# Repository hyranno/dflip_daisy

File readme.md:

WIP keyboard design

## Required Kicad Plugins (Manually via PCM):
* com.github.perigoso.keyswitch-kicad-library
* com.github.gauravmm.hierarchicalpcb
* com.github.yaqwsx.kikit

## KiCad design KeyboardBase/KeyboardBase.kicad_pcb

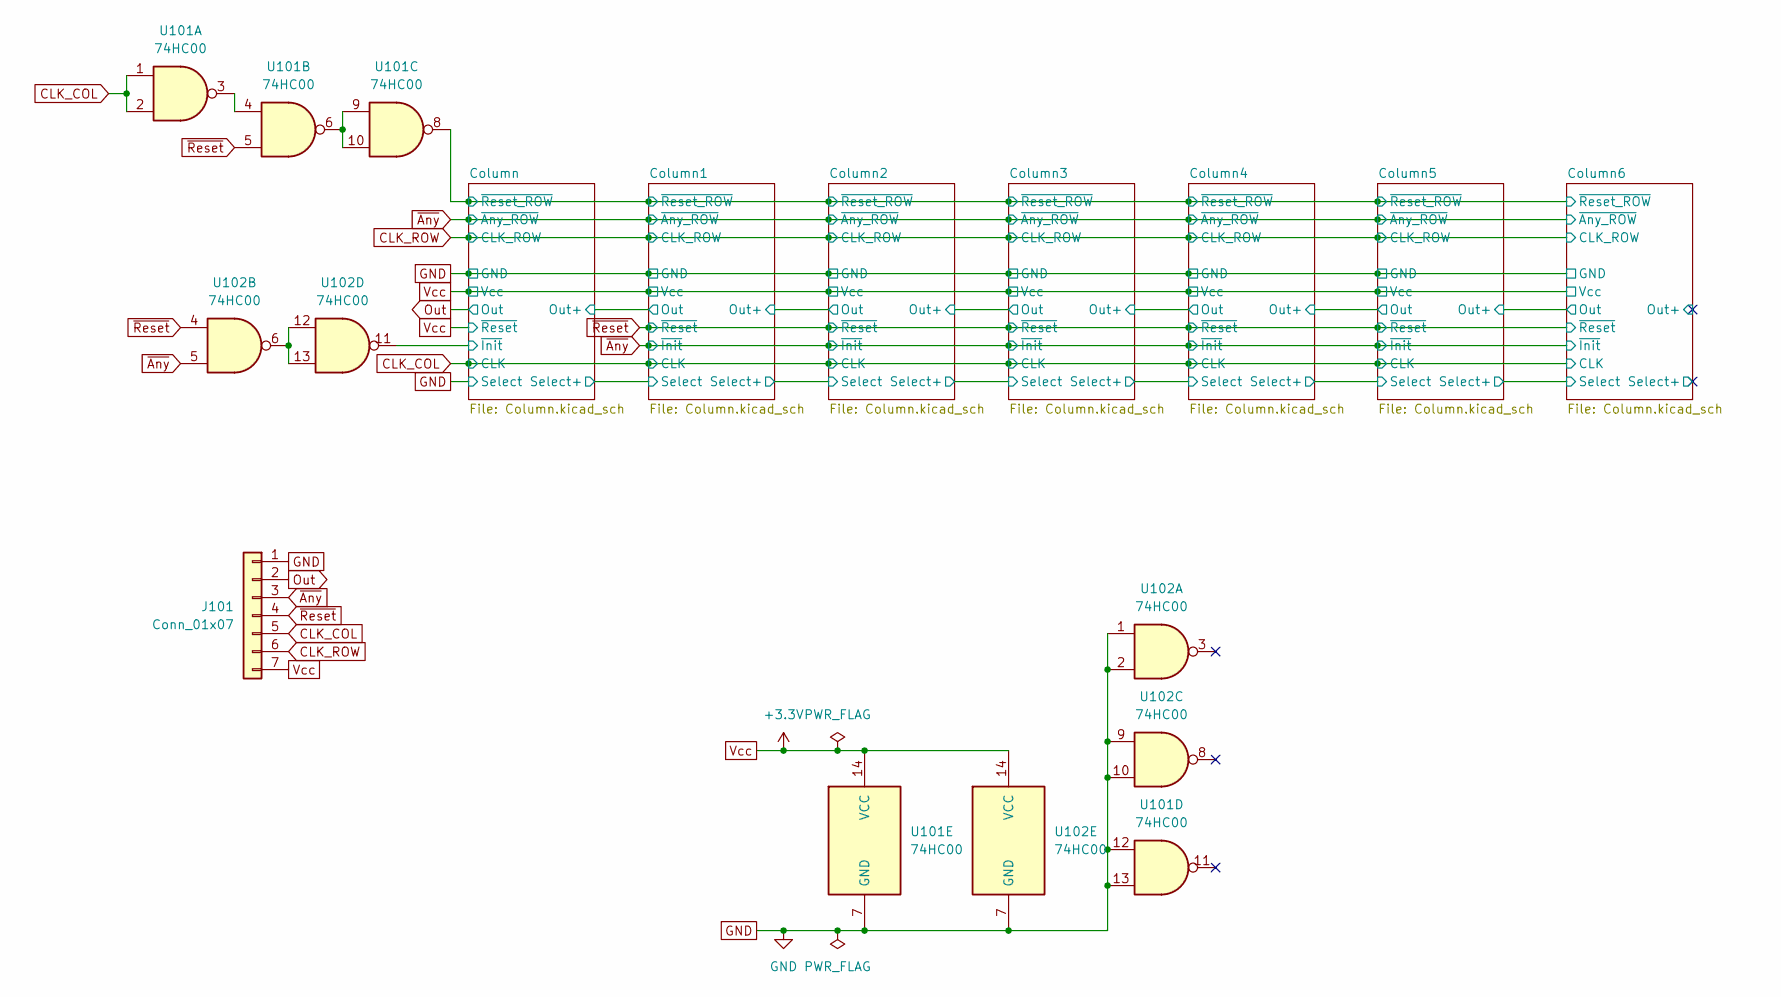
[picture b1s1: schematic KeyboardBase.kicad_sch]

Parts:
J101: Conn_01x07; PinHeader 2.00mm 01x07 SMD
U101, U102: 74HC00; WQFN-14-1EP_2.5x2.5mm_P0.5mm_EP1.45x1.45mm

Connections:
/Column/~Init: U102.11; also elsewhere on the board
/Column/~Reset_ROW: U101.8; also elsewhere on the board
CLK_COL: J101.5, U101.1, U101.2; also elsewhere on the board
GND: J101.1, U101.7 (GND), U101.12, U101.13, U101.15, U102.1, U102.2, U102.7 (GND), U102.9, U102.10, U102.15; also elsewhere on the board
unnamed: U101.3, U101.4
unnamed: U101.6, U101.9, U101.10
unnamed: U102.6, U102.12, U102.13
Vcc: J101.7, U101.14 (VCC), U102.14 (VCC); also elsewhere on the board
~Any: J101.3, U102.5; also elsewhere on the board
~Reset: J101.4, U101.5, U102.4; also elsewhere on the board

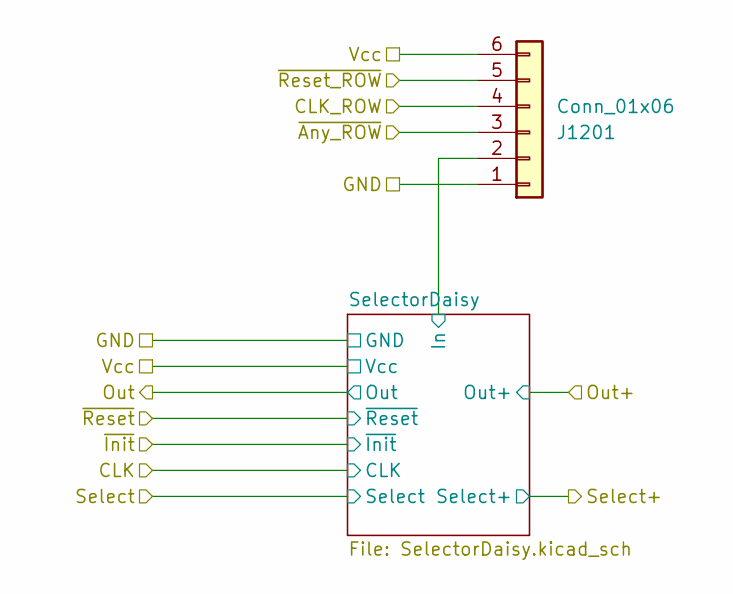
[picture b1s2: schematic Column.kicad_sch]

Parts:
J1201: Conn_01x06; Molex_200528-0060_1x06-1MP_P1.00mm_Horizontal; Manufacturer Part number 2005280060

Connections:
/Column5/SelectorDaisy/In: J1201.2; also elsewhere on the board
/Column/~Reset_ROW: J1201.5; also elsewhere on the board
CLK_ROW: J1201.4; also elsewhere on the board
GND: J1201.1; also elsewhere on the board
Vcc: J1201.6; also elsewhere on the board
~Any: J1201.3; also elsewhere on the board

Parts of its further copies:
J201, J401, J601, J801, J1001, J1401: Conn_01x06; Molex_200528-0060_1x06-1MP_P1.00mm_Horizontal; Manufacturer Part number 2005280060

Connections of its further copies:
/Column1/SelectorDaisy/In: J401.2; also elsewhere on the board
/Column2/SelectorDaisy/In: J601.2; also elsewhere on the board
/Column3/SelectorDaisy/In: J801.2; also elsewhere on the board
/Column4/SelectorDaisy/In: J1001.2; also elsewhere on the board
/Column6/SelectorDaisy/In: J1401.2; also elsewhere on the board
/Column/SelectorDaisy/In: J201.2; also elsewhere on the board
/Column/~Reset_ROW: J201.5, J401.5, J601.5, J801.5, J1001.5, J1401.5; also elsewhere on the board
CLK_ROW: J201.4, J401.4, J601.4, J801.4, J1001.4, J1401.4; also elsewhere on the board
GND: J201.1, J401.1, J601.1, J801.1, J1001.1, J1401.1; also elsewhere on the board
Vcc: J201.6, J401.6, J601.6, J801.6, J1001.6, J1401.6; also elsewhere on the board
~Any: J201.3, J401.3, J601.3, J801.3, J1001.3, J1401.3; also elsewhere on the board

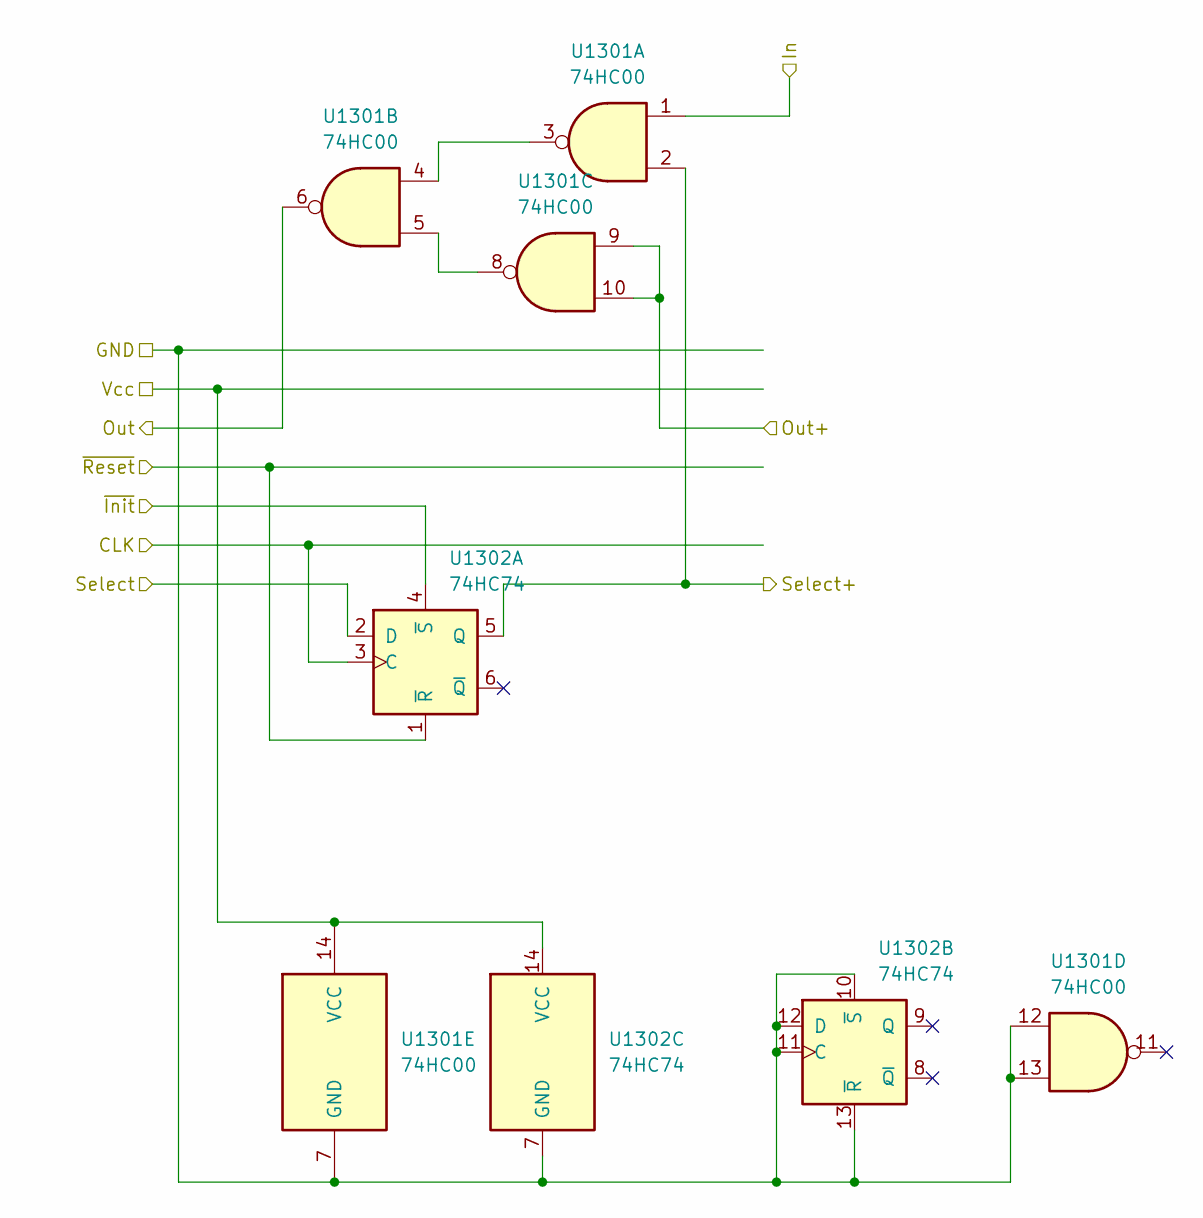
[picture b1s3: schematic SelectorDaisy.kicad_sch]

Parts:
U1301: 74HC00; WQFN-14-1EP_2.5x2.5mm_P0.5mm_EP1.45x1.45mm
U1302: 74HC74; WQFN-14-1EP_2.5x2.5mm_P0.5mm_EP1.45x1.45mm

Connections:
/Column4/Out+: U1301.6; also elsewhere on the board
/Column4/Select+: U1302.2 (D); also elsewhere on the board
/Column5/Out+: U1301.9, U1301.10; also elsewhere on the board
/Column5/Select+: U1301.2, U1302.5 (Q); also elsewhere on the board
/Column5/SelectorDaisy/In: U1301.1; also elsewhere on the board
CLK_COL: U1302.3 (C); also elsewhere on the board
GND: U1301.7 (GND), U1301.12, U1301.13, U1301.15, U1302.7 (GND), U1302.10 (~S), U1302.11 (C), U1302.12 (D), U1302.13 (~R), U1302.15; also elsewhere on the board
unnamed: U1301.3, U1301.4
unnamed: U1301.5, U1301.8
Vcc: U1301.14 (VCC), U1302.14 (VCC); also elsewhere on the board
~Any: U1302.4 (~S); also elsewhere on the board
~Reset: U1302.1 (~R); also elsewhere on the board

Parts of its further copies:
U301, U501, U701, U901, U1101, U1501: 74HC00; WQFN-14-1EP_2.5x2.5mm_P0.5mm_EP1.45x1.45mm
U302, U502, U702, U902, U1102, U1502: 74HC74; WQFN-14-1EP_2.5x2.5mm_P0.5mm_EP1.45x1.45mm

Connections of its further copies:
/Column1/Out+: U501.9, U501.10, U701.6
/Column1/Select+: U501.2, U502.5 (Q), U702.2 (D)
/Column1/SelectorDaisy/In: U501.1; also elsewhere on the board
/Column2/Out+: U701.9, U701.10, U901.6
/Column2/Select+: U701.2, U702.5 (Q), U902.2 (D)
/Column2/SelectorDaisy/In: U701.1; also elsewhere on the board
/Column3/Out+: U901.9, U901.10, U1101.6
/Column3/Select+: U901.2, U902.5 (Q), U1102.2 (D)
/Column3/SelectorDaisy/In: U901.1; also elsewhere on the board
/Column4/Out+: U1101.9, U1101.10; also elsewhere on the board
/Column4/Select+: U1101.2, U1102.5 (Q); also elsewhere on the board
/Column4/SelectorDaisy/In: U1101.1; also elsewhere on the board
/Column5/Out+: U1501.6; also elsewhere on the board
/Column5/Select+: U1502.2 (D); also elsewhere on the board
/Column6/Out+: U1501.9, U1501.10
/Column6/Select+: U1501.2, U1502.5 (Q)
/Column6/SelectorDaisy/In: U1501.1; also elsewhere on the board
/Column/Out+: U301.9, U301.10, U501.6
/Column/Select+: U301.2, U302.5 (Q), U502.2 (D)
/Column/SelectorDaisy/In: U301.1; also elsewhere on the board
/Column/~Init: U302.4 (~S); also elsewhere on the board
CLK_COL: U302.3 (C), U502.3 (C), U702.3 (C), U902.3 (C), U1102.3 (C), U1502.3 (C); also elsewhere on the board
GND: U301.7 (GND), U301.12, U301.13, U301.15, U302.2 (D), U302.7 (GND), U302.10 (~S), U302.11 (C), U302.12 (D), U302.13 (~R), U302.15, U501.7 (GND), U501.12, U501.13, U501.15, U502.7 (GND), U502.10 (~S), U502.11 (C), U502.12 (D), U502.13 (~R), U502.15, U701.7 (GND), U701.12, U701.13, U701.15, U702.7 (GND), U702.10 (~S), U702.11 (C), U702.12 (D), U702.13 (~R), U702.15, U901.7 (GND), U901.12, U901.13, U901.15, U902.7 (GND), U902.10 (~S), U902.11 (C), U902.12 (D), U902.13 (~R), U902.15, U1101.7 (GND), U1101.12, U1101.13, U1101.15, U1102.7 (GND), U1102.10 (~S), U1102.11 (C), U1102.12 (D), U1102.13 (~R), U1102.15, U1501.7 (GND), U1501.12, U1501.13, U1501.15, U1502.7 (GND), U1502.10 (~S), U1502.11 (C), U1502.12 (D), U1502.13 (~R), U1502.15; also elsewhere on the board
unnamed: U301.3, U301.4
unnamed: U301.5, U301.8
unnamed: U501.3, U501.4
unnamed: U501.5, U501.8
unnamed: U701.3, U701.4
unnamed: U701.5, U701.8
unnamed: U901.3, U901.4
unnamed: U901.5, U901.8
unnamed: U1101.3, U1101.4
unnamed: U1101.5, U1101.8
unnamed: U1501.3, U1501.4
unnamed: U1501.5, U1501.8
Out: U301.6; also elsewhere on the board
Vcc: U301.14 (VCC), U302.1 (~R), U302.14 (VCC), U501.14 (VCC), U502.14 (VCC), U701.14 (VCC), U702.14 (VCC), U901.14 (VCC), U902.14 (VCC), U1101.14 (VCC), U1102.14 (VCC), U1501.14 (VCC), U1502.14 (VCC); also elsewhere on the board
~Any: U502.4 (~S), U702.4 (~S), U902.4 (~S), U1102.4 (~S), U1502.4 (~S); also elsewhere on the board
~Reset: U502.1 (~R), U702.1 (~R), U902.1 (~R), U1102.1 (~R), U1502.1 (~R); also elsewhere on the board

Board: 2 copper layers, 24 parts (0 on the bottom side), 47 nets, no tracks yet.

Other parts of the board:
J102: 5023520701; CONN07_502352_MOL

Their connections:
CLK_COL: J102.3; also elsewhere on the board
CLK_ROW: J102.2; also elsewhere on the board
GND: J102.7; also elsewhere on the board
Out: J102.6; also elsewhere on the board
Vcc: J102.1; also elsewhere on the board
~Any: J102.5; also elsewhere on the board
~Reset: J102.4; also elsewhere on the board

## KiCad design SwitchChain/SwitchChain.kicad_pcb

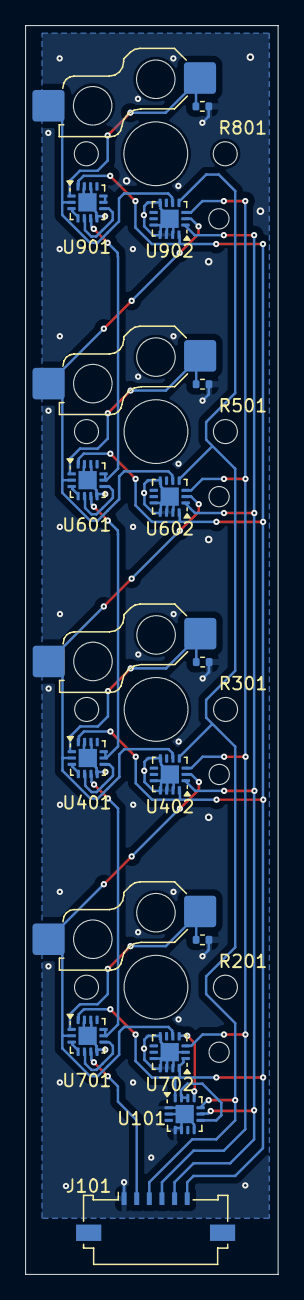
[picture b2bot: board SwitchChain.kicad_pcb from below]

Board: 2 copper layers, 20.0 x 98.9 mm, 18 parts (14 on the bottom side), 28 nets, no tracks yet.

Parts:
J101: Conn_01x06; Molex_200528-0060_1x06-1MP_P1.00mm_Horizontal
R201, R301, R501, R801: 40k; R_0402_1005Metric
SW201, SW301, SW501, SW801: SW_Push; SW_Hotswap_Kailh_Choc_V1V2_1.00u
U101, U401, U601, U701, U901: 74HC00; WQFN-14-1EP_2.5x2.5mm_P0.5mm_EP1.45x1.45mm
U402, U602, U702, U902: 74HC74; WQFN-14-1EP_2.5x2.5mm_P0.5mm_EP1.45x1.45mm

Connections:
/SwitchDaisy1/Out+: U401.9, U401.10, U601.6
/SwitchDaisy1/Select+: SW301.2, U401.2, U402.5 (Q), U602.2 (D)
/SwitchDaisy1/SelectorDaisy/In: R301.1, SW301.1, U401.1
/SwitchDaisy2/Out+: U601.9, U601.10, U901.6
/SwitchDaisy2/Select+: SW501.2, U601.2, U602.5 (Q), U902.2 (D)
/SwitchDaisy2/SelectorDaisy/In: R501.1, SW501.1, U601.1
/SwitchDaisy3/Out+: U901.9, U901.10
/SwitchDaisy3/Select+: SW801.2, U901.2, U902.5 (Q)
/SwitchDaisy3/SelectorDaisy/In: R801.1, SW801.1, U901.1
/SwitchDaisy/Out+: U401.6, U701.9, U701.10
/SwitchDaisy/Select+: SW201.2, U402.2 (D), U701.2, U702.5 (Q)
/SwitchDaisy/SelectorDaisy/In: R201.1, SW201.1, U701.1
/SwitchDaisy/~Init: U101.11, U702.4 (~S)
CLK: J101.4, U402.3 (C), U602.3 (C), U702.3 (C), U902.3 (C)
GND: J101.1, R201.2, R301.2, R501.2, R801.2, U101.1, U101.2, U101.4, U101.5, U101.7 (GND), U101.15, U401.7 (GND), U401.12, U401.13, U401.15, U402.7 (GND), U402.10 (~S), U402.11 (C), U402.12 (D), U402.13 (~R), U402.15, U601.7 (GND), U601.12, U601.13, U601.15, U602.7 (GND), U602.10 (~S), U602.11 (C), U602.12 (D), U602.13 (~R), U602.15, U701.7 (GND), U701.12, U701.13, U701.15, U702.2 (D), U702.7 (GND), U702.10 (~S), U702.11 (C), U702.12 (D), U702.13 (~R), U702.15, U901.7 (GND), U901.12, U901.13, U901.15, U902.7 (GND), U902.10 (~S), U902.11 (C), U902.12 (D), U902.13 (~R), U902.15
unnamed: U101.8, U101.12, U101.13
unnamed: U401.3, U401.4
unnamed: U401.5, U401.8
unnamed: U601.3, U601.4
unnamed: U601.5, U601.8
unnamed: U701.3, U701.4
unnamed: U701.5, U701.8
unnamed: U901.3, U901.4
unnamed: U901.5, U901.8
Out: J101.2, U701.6
Vcc: J101.6, U101.14 (VCC), U401.14 (VCC), U402.14 (VCC), U601.14 (VCC), U602.14 (VCC), U701.14 (VCC), U702.1 (~R), U702.14 (VCC), U901.14 (VCC), U902.14 (VCC)
~Any: J101.3, U101.10, U402.4 (~S), U602.4 (~S), U902.4 (~S)
~Reset: J101.5, U101.9, U402.1 (~R), U602.1 (~R), U902.1 (~R)

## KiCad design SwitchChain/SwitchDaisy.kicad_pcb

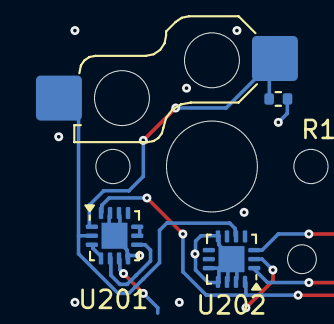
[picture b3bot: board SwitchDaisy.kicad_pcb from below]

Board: 2 copper layers, 4 parts (3 on the bottom side), 7 nets, no tracks yet.

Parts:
R101: 40k; R_0402_1005Metric
SW101: SW_Push; SW_Hotswap_Kailh_Choc_V1V2_1.00u
U201: 74HC00; WQFN-14-1EP_2.5x2.5mm_P0.5mm_EP1.45x1.45mm
U202: 74HC74; WQFN-14-1EP_2.5x2.5mm_P0.5mm_EP1.45x1.45mm

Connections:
/GND: R101.2, U201.7 (GND), U201.12, U201.13, U201.15, U202.7 (GND), U202.10 (~S), U202.11 (C), U202.12 (D), U202.13 (~R), U202.15
/Out+: U201.9, U201.10
/Select+: SW101.2, U201.2, U202.5 (Q)
/SelectorDaisy/In: R101.1, SW101.1, U201.1
/Vcc: U201.14 (VCC), U202.14 (VCC)
unnamed: U201.3, U201.4
unnamed: U201.5, U201.8

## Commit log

2024-12-27 add devcontainer
2024-12-30 fix devcontainer
2024-12-31 add rmk
2024-12-31 add vscode extension for devcontainer
2025-01-01 init rmk
2025-01-01 add gitignore for rmk
2025-01-01 add vscode extension
2025-01-01 rmk init monolithic
2025-01-02 use internal matrix definition
2025-01-03 custom matrix for rmk
2025-01-03 fix pin label, reduce column keys to 4
2025-01-03 move custom rmk device outside
2025-01-21 add .gitignore entry
2025-01-22 add simcir circuit simulation
2025-01-23 fix circuit
2025-01-24 change connector
2025-01-24 flip connector
2025-01-24 remove padding
2025-01-26 add kikit
2025-01-26 move files
